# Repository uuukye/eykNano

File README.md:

# eykPad_nano
A small electronic pad used for timer and other cool stuff!
<br><br><br>

3D pcb image:

<br><br>
2D pcb image:

<br><br>
eykNano is a multifunctional pad. It has a RaspberryPi Pico microcontroller, and is minimalistic and compact. (67x62mm)
The microcontroller is a RaspberryPi Pico, so it has a built in Micro-USB Type-B port.

<br><br>
Schematic image:

The schematic is pretty simple. In the project, I added <b>nine</b> led lights, each with different color, <b>three</b> 
buttons (settings, next light, ok), and a 7 segment display (one digit, can allow useful features or games.

I will start with these basic three functions for this: 

-<b>A binary timer</b>. the lights represent minutes/seconds. The first light is 30 seconds, the second light is 1 minute, the third light is 2 minutes, and it doubles every light. That means you can set a timer for any multiple of 30 seconds up to 4 hours, 15 minutes and 30 seconds. When the timer is almost up (less than 10 seconds) the 7 segment LED display will count down. and once the timer ends, the LEDS flash on and off.

-<b>A memory game.</b> The nine lights will play a sequence, and you use the buttons to recreate the sequence. Like a normal memory game, it will become longer and harder over time, building up on the last sequence.

-<b>A reaction time test.</b> All the LEDS will flash on for a few seconds (randomized) and they will all turn off at the same time. The player has to press the (OK) button. Then, the lights will represent (in binary, milliseconds) how much time it took for you to press the button. (I might deduct a few milliseconds if there is a delay on pressing the button and the lights turning off)

Of course, that's not the only functions I will put for this project. I will add more cool features eventually.

<br><br>
BOM:

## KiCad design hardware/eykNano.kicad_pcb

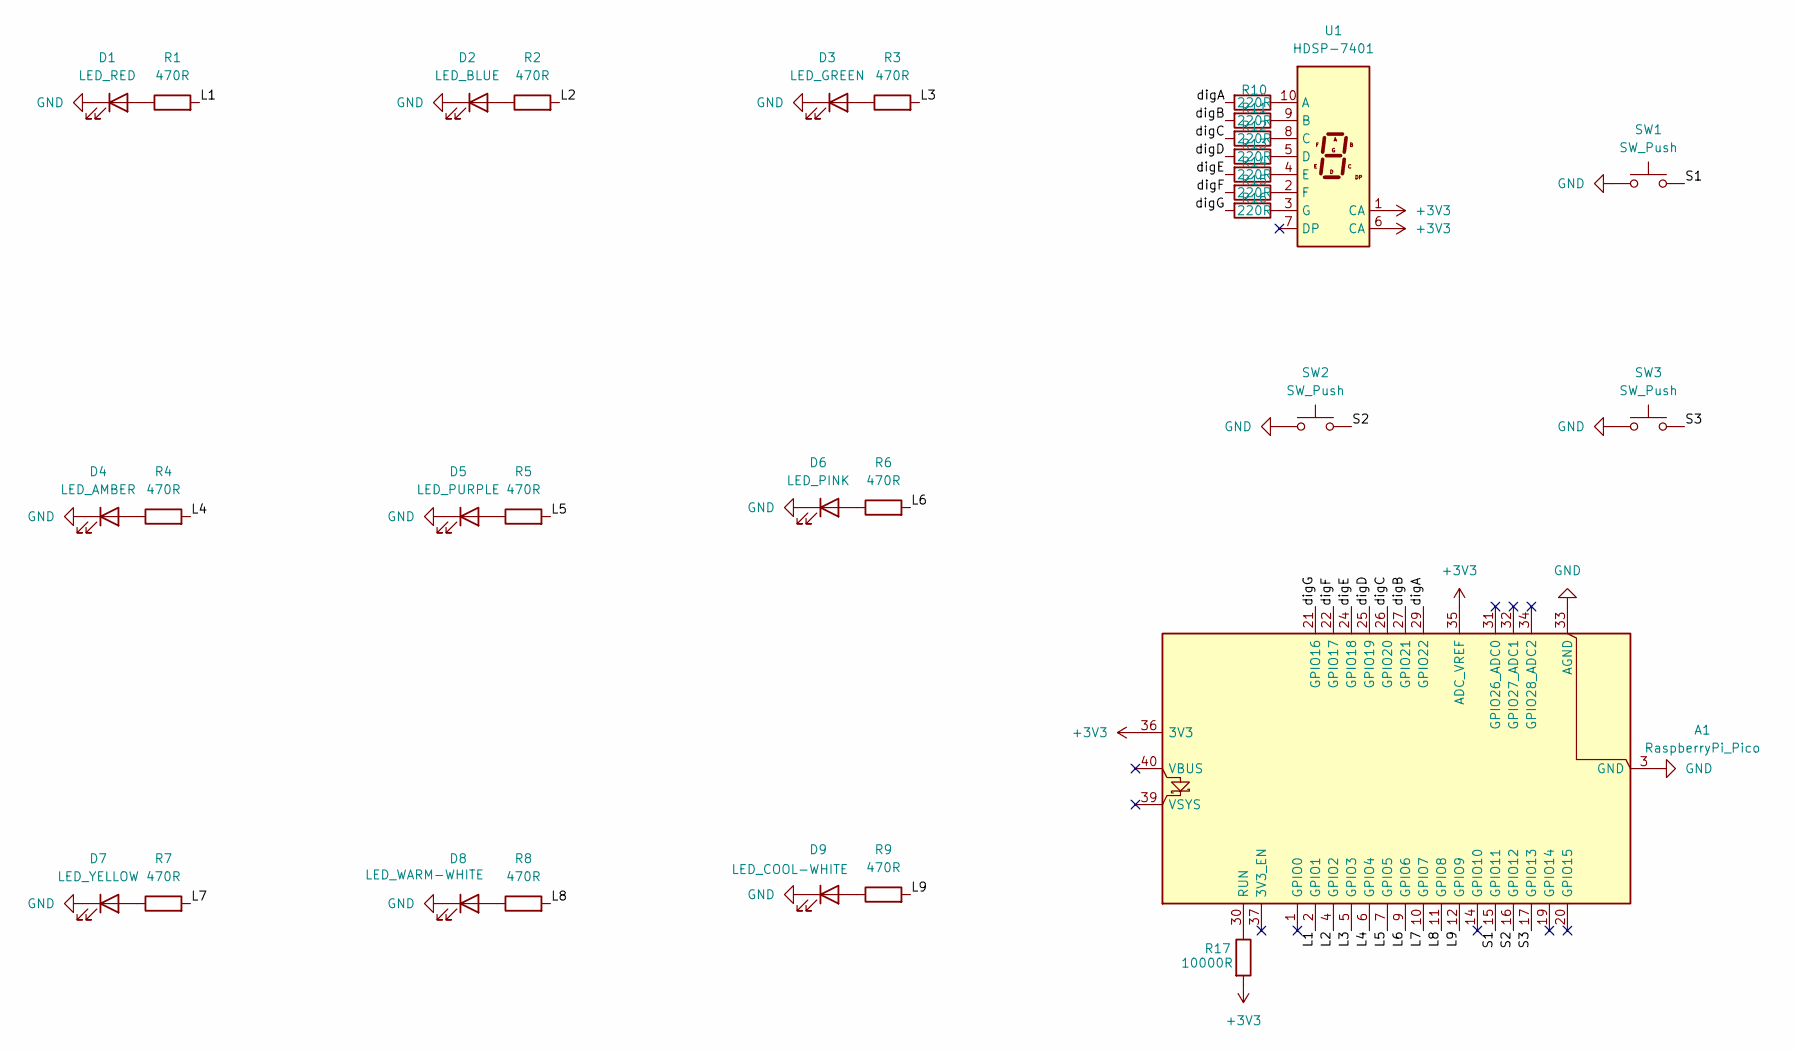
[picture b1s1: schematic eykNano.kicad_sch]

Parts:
A1: RaspberryPi_Pico; RaspberryPi_Pico_SMD_HandSolder
D1: LED_RED; LED_0805_2012Metric
D2: LED_BLUE; LED_0805_2012Metric
D3: LED_GREEN; LED_0805_2012Metric
D4: LED_AMBER; LED_0805_2012Metric
D5: LED_PURPLE; LED_0805_2012Metric
D6: LED_PINK; LED_0805_2012Metric
D7: LED_YELLOW; LED_0805_2012Metric
D8: LED_WARM-WHITE; LED_0805_2012Metric
D9: LED_COOL-WHITE; LED_0805_2012Metric
R1, R2, R3, R4, R5, R6, R7, R8, R9: 470R; R_0805_2012Metric
R10, R11, R12, R13, R14, R15, R16: 220R; R_0805_2012Metric
R17: 10000R; R_0805_2012Metric
SW1, SW2, SW3: SW_Push; SW_Push_1P1T_NO_E-Switch_TL3301NxxxxxG
U1: HDSP-7401

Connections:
+3V3: A1.35 (ADC_VREF), A1.36 (3V3), R17.2, U1.1 (CA), U1.6 (CA)
/L1: A1.2 (GPIO1), R1.2
/L2: A1.4 (GPIO2), R2.2
/L3: A1.5 (GPIO3), R3.2
/L4: A1.6 (GPIO4), R4.2
/L5: A1.7 (GPIO5), R5.2
/L6: A1.9 (GPIO6), R6.2
/L7: A1.10 (GPIO7), R7.2
/L8: A1.11 (GPIO8), R8.2
/L9: A1.12 (GPIO9), R9.2
/S1: A1.15 (GPIO11), SW1.2
/S2: A1.16 (GPIO12), SW2.2
/S3: A1.17 (GPIO13), SW3.2
/digA: A1.29 (GPIO22), R10.2
/digB: A1.27 (GPIO21), R11.2
/digC: A1.26 (GPIO20), R12.2
/digD: A1.25 (GPIO19), R13.2
/digE: A1.24 (GPIO18), R14.2
/digF: A1.22 (GPIO17), R15.2
/digG: A1.21 (GPIO16), R16.2
GND: A1.3 (GND), A1.8 (GND), A1.13 (GND), A1.18 (GND), A1.23 (GND), A1.28 (GND), A1.33 (AGND), A1.38 (GND), D1.1 (K), D2.1 (K), D3.1 (K), D4.1 (K), D5.1 (K), D6.1 (K), D7.1 (K), D8.1 (K), D9.1 (K), SW1.1, SW2.1, SW3.1
unnamed: A1.30 (RUN), R17.1
unnamed: D1.2 (A), R1.1
unnamed: D2.2 (A), R2.1
unnamed: D3.2 (A), R3.1
unnamed: D4.2 (A), R4.1
unnamed: D5.2 (A), R5.1
unnamed: D6.2 (A), R6.1
unnamed: D7.2 (A), R7.1
unnamed: D8.2 (A), R8.1
unnamed: D9.2 (A), R9.1
unnamed: R10.1, U1.10 (A)
unnamed: R11.1, U1.9 (B)
unnamed: R12.1, U1.8 (C)
unnamed: R13.1, U1.5 (D)
unnamed: R14.1, U1.4 (E)
unnamed: R15.1, U1.2 (F)
unnamed: R16.1, U1.3 (G)

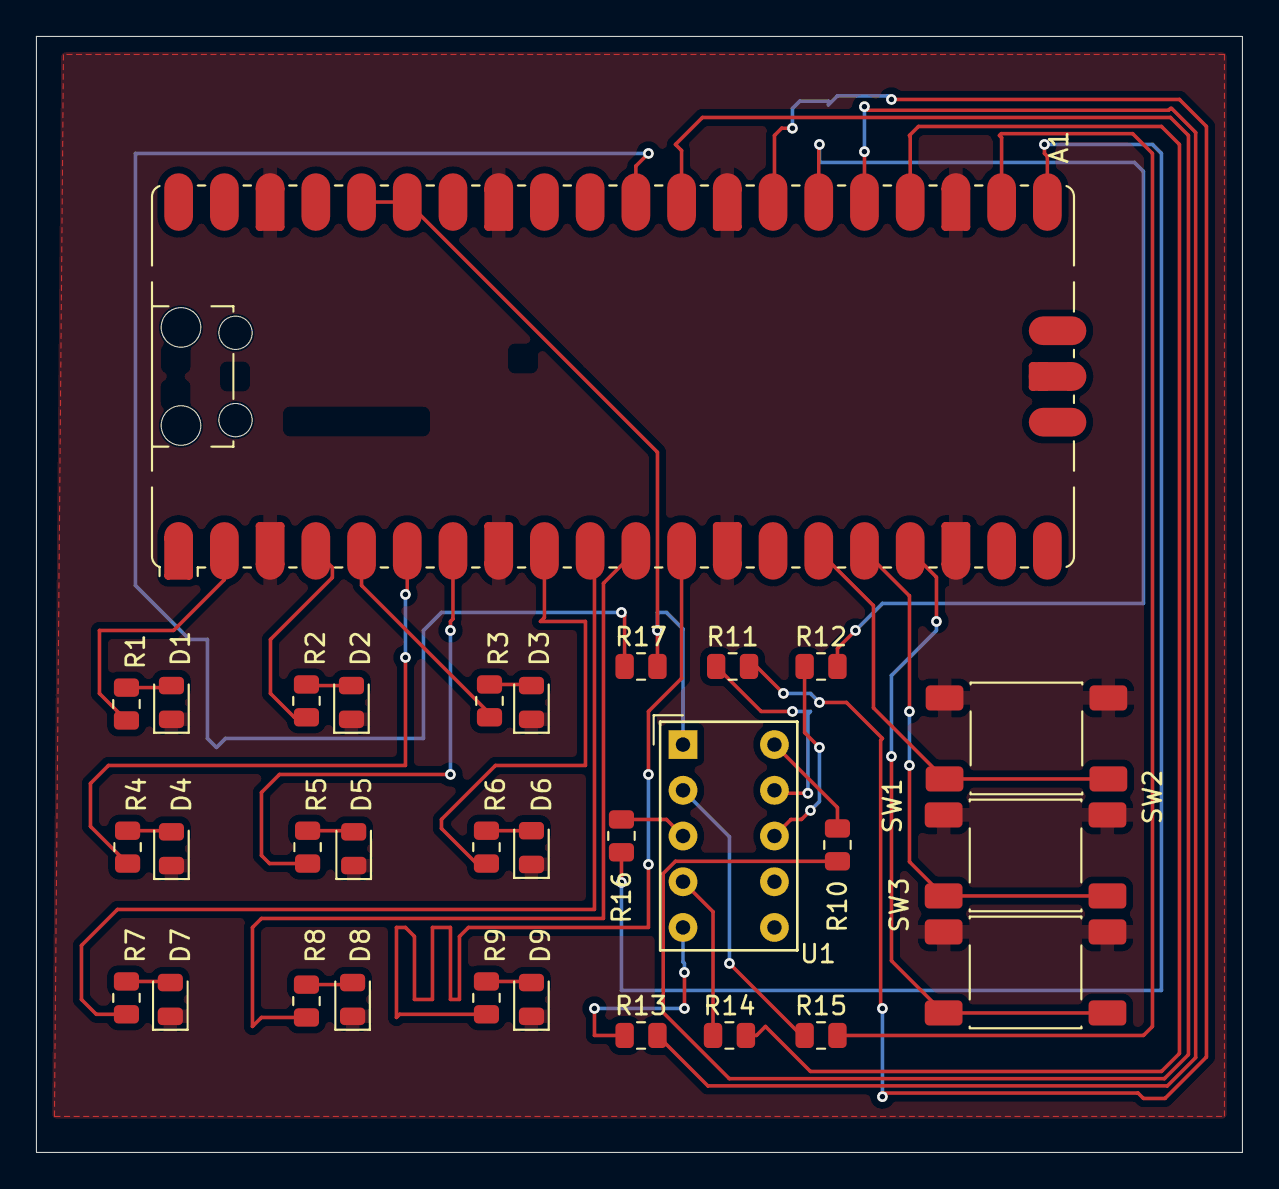
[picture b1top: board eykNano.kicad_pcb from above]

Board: 2 copper layers, 67.0 x 62.0 mm, 31 parts (0 on the bottom side), 38 nets.

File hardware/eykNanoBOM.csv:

Reference,Qty,Value,DNP,Exclude from BOM,Exclude from Board,Exclude from Simulation,Exclude from Position Files,Footprint,Datasheet,Link,Linked_MPN,Footprint_Check,Verification_Source
A1,1,RaspberryPi_Pico,,,,,${EXCLUDE_FROM_POS_FILES},Module:RaspberryPi_Pico_SMD_HandSolder,https://datasheets.raspberrypi.com/pico/pico-datasheet.pdf,https://www.raspberrypi.com/products/raspberry-pi-pico/,Raspberry Pi Pico,PASS — Pico SMT footprint documented by Raspberry Pi; keep the BOM footprint exactly as shown.,https://pip-assets.raspberrypi.com/categories/610-raspberry-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
D1,1,LED_RED,,,,,${EXCLUDE_FROM_POS_FILES},LED_SMD:LED_0805_2012Metric,,https://www.digikey.com/en/products/detail/lumex-opto-compon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,SML-LX0805IC-TR,PASS — DigiKey lists 0805 (2012 Metric); compatible with LED_SMD:LED_0805_2012Metric.,https://kicad.github.io/footprints/LED_SMD.html
D2,1,LED_BLUE,,,,,${EXCLUDE_FROM_POS_FILES},LED_SMD:LED_0805_2012Metric,,https://www.digikey.com/en/products/detail/bivar-inc/SM0805U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,SM0805UBWC,PASS — DigiKey lists 0805 (2012 Metric); compatible with LED_SMD:LED_0805_2012Metric.,https://kicad.github.io/footprints/LED_SMD.html
D3,1,LED_GREEN,,,,,${EXCLUDE_FROM_POS_FILES},LED_SMD:LED_0805_2012Metric,,https://www.digikey.com/en/products/detail/bivar-inc/SM0805G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,SM0805GCL,PASS — DigiKey lists 0805 (2012 Metric); compatible with LED_SMD:LED_0805_2012Metric.,https://kicad.github.io/footprints/LED_SMD.html
D4,1,LED_AMBER,,,,,${EXCLUDE_FROM_POS_FILES},LED_SMD:LED_0805_2012Metric,,https://www.digikey.com/en/products/detail/bivar-inc/SM0805A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,SM0805AC,PASS — DigiKey lists 0805 (2012 Metric); compatible with LED_SMD:LED_0805_2012Metric.,https://kicad.github.io/footprints/LED_SMD.html
D5,1,LED_PURPLE,,,,,${EXCLUDE_FROM_POS_FILES},LED_SMD:LED_0805_2012Metric,,https://www.digikey.com/en/products/detail/yongyu-optoelectr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,YY0805PU-NN1S0-T3AR4,"PASS — DigiKey lists 0805 (2012 Metric), surface mount, standard 2-terminal LED; compatible with LED_SMD:LED_0805_2012Metric.",https://kicad.github.io/footprints/LED_SMD.html
D6,1,LED_PINK,,,,,${EXCLUDE_FROM_POS_FILES},LED_SMD:LED_0805_2012Metric,,https://www.digikey.com/en/products/detail/xinglight/XL-2012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,XL-2012UPC,"PASS — DigiKey lists 0805 (2012 Metric), surface mount, standard independent LED; compatible with LED_SMD:LED_0805_2012Metric.",https://kicad.github.io/footprints/LED_SMD.html
D7,1,LED_YELLOW,,,,,${EXCLUDE_FROM_POS_FILES},LED_SMD:LED_0805_2012Metric,,https://www.digikey.com/en/products/detail/bivar-inc/SM0805Y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,SM0805YCL,PASS — DigiKey lists 0805 (2012 Metric); compatible with LED_SMD:LED_0805_2012Metric.,https://kicad.github.io/footprints/LED_SMD.html
D8,1,LED_WARM-WHITE,,,,,${EXCLUDE_FROM_POS_FILES},LED_SMD:LED_0805_2012Metric,,https://www.digikey.com/en/products/detail/xinglight/XL-2012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,XL-2012WWC,"PASS — DigiKey lists 0805 (2012 Metric), surface mount; compatible with LED_SMD:LED_0805_2012Metric.",https://kicad.github.io/footprints/LED_SMD.html
D9,1,LED_COOL-WHITE,,,,,${EXCLUDE_FROM_POS_FILES},LED_SMD:LED_0805_2012Metric,,https://www.digikey.com/en/products/detail/liteon/LTW-170TK/758704,LTW-170TK,"PASS — DigiKey lists standard 0805 (2012 Metric), surface mount. Optical color is listed as White (not specifically Cool White), so footprint is verified but color is not an exact match.",https://kicad.github.io/footprints/LED_SMD.html
"R1,R2,R3,R4,R5,R6,R7,R8,R9",9,470R,,,,,${EXCLUDE_FROM_POS_FILES},Resistor_SMD:R_0805_2012Metric,,https://www.digikey.com/en/products/detail/yageo/RC0805JR-07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,RC0805JR-07470RP,"PASS — DigiKey lists 0805 (2012 Metric), 2-terminal chip resistor; compatible with Resistor_SMD:R_0805_2012Metric.",https://kicad.github.io/footprints/Resistor_SMD.html
"R10,R11,R12,R13,R14,R15,R16",7,220R,,,,,${EXCLUDE_FROM_POS_FILES},Resistor_SMD:R_0805_2012Metric,,https://www.digikey.com/en/products/detail/yageo/AC0805FR-7W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,AC0805FR-7W220RL,"PASS — DigiKey lists 0805 (2012 Metric), 2-terminal chip resistor; compatible with Resistor_SMD:R_0805_2012Metric.",https://kicad.github.io/footprints/Resistor_SMD.html
R17,1,10000R,,,,,${EXCLUDE_FROM_POS_FILES},Resistor_SMD:R_0805_2012Metric,,https://www.digikey.com/en/products/detail/yageo/AC0805FR-7W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,AC0805FR-7W10KL,"PASS — DigiKey lists 0805 (2012 Metric), 2-terminal chip resistor; compatible with Resistor_SMD:R_0805_2012Metric.",https://kicad.github.io/footprints/Resistor_SMD.html
"SW1,SW2,SW3",3,SW_Push,,,,,${EXCLUDE_FROM_POS_FILES},Button_Switch_SMD:SW_Push_1P1T_NO_E-Switch_TL3301NxxxxxG,,https://www.digikey.com/en/products/detail/e-switch/TL3301NF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,TL3301NF160QG-KR,"PASS — DigiKey lists TL3301 series, 6.00 x 6.00 mm, top-actuated SMD, gull-wing; this is the family targeted by the BOM footprint name.",https://www.digikey.com/en/products/category/switches/15
U1,1,HDSP-7401,,,,,${EXCLUDE_FROM_POS_FILES},Display_7Segment:HDSP-7401,https://docs.broadcom.com/docs/AV02-2553EN,https://www.digikey.com/en/products/detail/broadcom-limited/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,HDSP-7401,"PASS — Exact MPN. DigiKey lists 10-DIP, 0.200 in / 5.08 mm pitch; KiCad has a dedicated Display_7Segment:HDSP-7401 footprint.",https://kicad.github.io/footprints/Display_7Segment.html
